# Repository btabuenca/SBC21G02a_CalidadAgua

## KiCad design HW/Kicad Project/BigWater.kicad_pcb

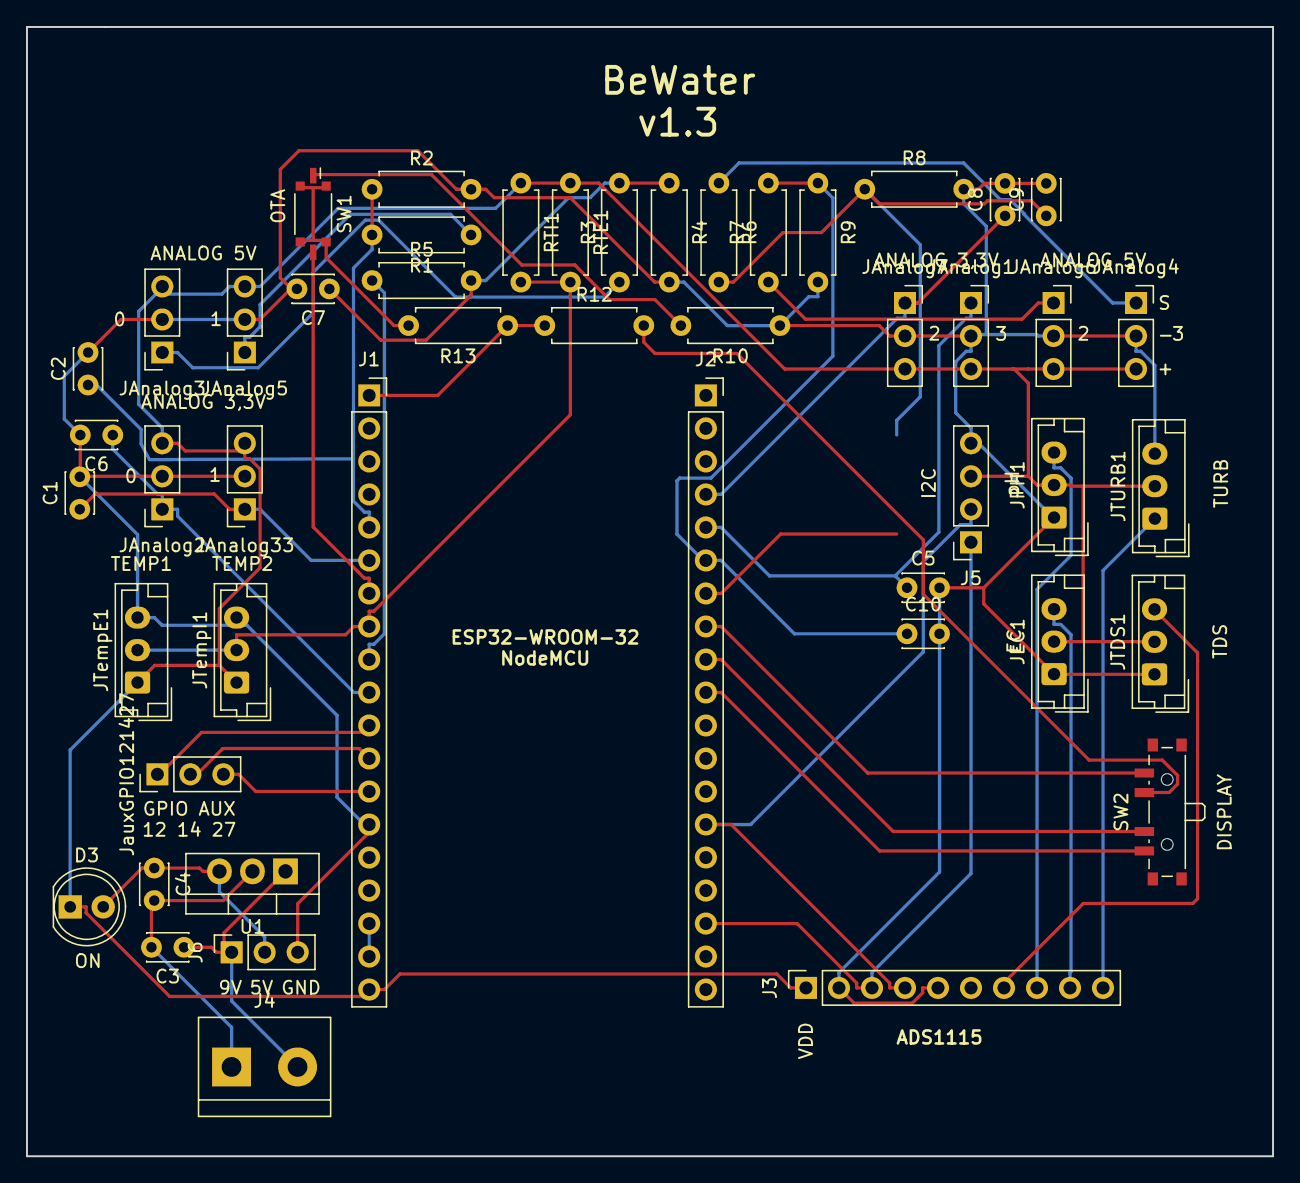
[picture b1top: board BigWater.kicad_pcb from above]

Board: 2 copper layers, 95.9 x 86.9 mm, 49 parts (0 on the bottom side), 37 nets.

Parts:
C1, C2, C4, C5, C6, C7, C8, C9, C10: 0.1u; C_Disc_D3.0mm_W2.0mm_P2.50mm
C3: 0.33u; C_Disc_D3.0mm_W2.0mm_P2.50mm
D3: LED; LED_D5.0mm
J1, J2: Conn_01x19; PinSocket_1x19_P2.54mm_Vertical
J3: ADS1115; PinSocket_1x10_P2.54mm_Vertical
J4: Conn_01x02; TerminalBlock_bornier-2_P5.08mm
J5: I2C; PinSocket_1x04_P2.54mm_Vertical
J6: Conn_01x03; PinSocket_1x03_P2.54mm_Vertical
JAnalog1, JAnalog2, JAnalog3, JAnalog4, JAnalog5, JAnalog6, JAnalog7, JAnalog33: Conn_01x03; PinSocket_1x03_P2.54mm_Vertical
JEC1: Conn_01x03; JST_EH_B3B-EH-A_1x03_P2.50mm_Vertical
JPH1: Conn_01x03; JST_EH_B3B-EH-A_1x03_P2.50mm_Vertical
JTDS1: Conn_01x03; JST_EH_B3B-EH-A_1x03_P2.50mm_Vertical
JTURB1: Conn_01x03; JST_EH_B3B-EH-A_1x03_P2.50mm_Vertical
JTempE1: Conn_01x03; JST_EH_B3B-EH-A_1x03_P2.50mm_Vertical
JTempI1: Conn_01x03; JST_EH_B3B-EH-A_1x03_P2.50mm_Vertical
JauxGPIO121427: Conn_01x03; PinHeader_1x03_P2.54mm_Vertical
R1, R3, R6, R7, R10, R12, R13: 1K; R_Axial_DIN0207_L6.3mm_D2.5mm_P7.62mm_Horizontal
R2, R4, R8, R9: 2K; R_Axial_DIN0207_L6.3mm_D2.5mm_P7.62mm_Horizontal
R5: 100; R_Axial_DIN0207_L6.3mm_D2.5mm_P7.62mm_Horizontal
RTE1: 4K7; R_Axial_DIN0207_L6.3mm_D2.5mm_P7.62mm_Horizontal
RTI1: 4K7; R_Axial_DIN0207_L6.3mm_D2.5mm_P7.62mm_Horizontal
SW1: SW_SPDT; SW_DIP_SPSTx01_Slide_Copal_CVS-01xB_W5.9mm_P1mm
SW2: SW_SP3T; SW_SP3T_PCM13
U1: LM7805_TO220; TO-220-3_Vertical

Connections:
5V: D3.1, J1.19, J3.1, J5.3, JAnalog1.3, JAnalog2.3, JAnalog3.3, JAnalog4.3, JAnalog5.3, JAnalog6.3, JAnalog7.3, JAnalog33.3, JEC1.2, JPH1.2, JTDS1.2, JTURB1.2, JTempE1.1, JTempI1.1, RTE1.1, RTI1.1
33V: J1.1, R12.1, R13.1
ANALOG5: C2.1, J1.5, R1.2, R2.1
ANALOG5b: J1.9, R5.1
ANALOG5c: C9.1, J2.7, R6.2, R8.1
ANALOG5d: C10.1, J2.6, R7.2, R9.1
ANALOG33: C1.1, J1.6, JAnalog33.1
ANALOG33b: C6.1, J1.10, JAnalog2.1
ANALOG33c: C5.1, J2.5, JAnalog1.1
ANALOG33d: C8.1, J2.4, JAnalog7.1
Aux12: J1.13, JauxGPIO121427.3
Aux14: J1.12, JauxGPIO121427.2
Aux27: J1.11, JauxGPIO121427.1
EC: J3.9, JEC1.3
GND: C1.2, C2.2, C5.2, C6.2, C7.2, C8.2, C9.2, C10.2, J1.14, J3.2, J3.5, J5.4, J6.3, JAnalog1.2, JAnalog2.2, JAnalog3.2, JAnalog4.2, JAnalog5.2, JAnalog6.2, JAnalog7.2, JAnalog33.2, JEC1.1, JPH1.1, JTDS1.1, JTURB1.3, JTempE1.3, JTempI1.3, R2.2, R4.2, R8.2, R9.2, R10.1
unnamed: C3.1, J4.2, J6.1, U1.1
unnamed: C3.2, C4.2, J4.1, U1.2
unnamed: C4.1, D3.2, J6.2, U1.3
unnamed: C7.1, R3.2, R4.1, R5.2
unnamed: JAnalog3.1, R3.1
unnamed: JAnalog4.1, R6.1
unnamed: JAnalog5.1, R1.1
unnamed: JAnalog6.1, R7.1
unnamed: R10.2, SW1.1
unnamed: R12.2, SW2.3
unnamed: R13.2, SW1.3
OTA: J1.7, SW1.2
OneWire: J1.8, JTempE1.2, JTempI1.2, RTE1.2, RTI1.2
SCL: J2.17, J3.3, J5.1
SDA: J2.14, J3.4, J5.2
SPI_HD: J1.17, J1.18
TDS: J3.7, JTDS1.3
TURB: J3.10, JTURB1.1
display1: J2.10, SW2.1
display2: J2.9, SW2.2
display3: J2.8, SW2.4
pH: J3.8, JPH1.3

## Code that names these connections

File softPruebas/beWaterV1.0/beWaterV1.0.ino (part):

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#define TOKEN               "ESP32_BeWater_SBC"
#define THINGSBOARD_SERVER  "thingsboard.cloud"
#define SERIAL_DEBUG_BAUD 115200
#define PIN_OTA 34
#define PERIODO 10
#define SEGUNDOSOTA 300 //Segundos que permanecerá el dispositivo disponible para OTA
#define CALVTURB 0
#define KHIGHEC 0.9
#define KLOWEC 1.1
#define OFFSETPH 0
#define uS_TO_S_FACTOR 1000000ULL  
#define DISPLAY1 32
#define DISPLAY2 35
#define DISPLAY3 27
#define PIN_TEMP 33
#define SAMPLESpH 16
#define SECS_DISPLAY 30
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WebServer server(80);

//Sensors
OneWire oneWireObjeto(PIN_TEMP);
DallasTemperature sensorDS18B20(&oneWireObjeto);
WiFiClient espClient;
ThingsBoard tb(espClient);
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   
   sensorDS18B20.begin();
   ads.begin();
   pinMode(PIN_OTA, INPUT);
   pinMode(DISPLAY1, INPUT);
   pinMode(DISPLAY2, INPUT);
   pinMode(DISPLAY3, INPUT);
   attachInterrupt(DISPLAY3, isr, RISING);
   lcd.init();                      
   lcd.backlight();
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void loop() {
  wakeup();
  initConection();
  if(digitalRead(PIN_OTA) == RISING){
    ndor=hour;
    }
  if(ndor==hour){      // ciclos para ser lanzado cada hora
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
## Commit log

2021-10-28 Subidos programas de obtencion de temperatura por puerto 33
2021-10-28 Subidos ficheros para funcionamiento de thingsboard
2021-11-04 Cambios en el pin de entrada de datos. Ahora es el 33
2021-11-04 Conseguida conexión con thingsboard
2021-11-04 Conseguida conexión de temp y turbidez
2021-11-18 Reestructurado el programa
2021-11-18 Falta revisar funcion de transformacion de voltajea turbidez
2021-11-23 Arreglado CAD para sensor de turbidez
2021-11-24 Añadido archivo para animación inicial
2021-11-25 Añadido modo bajo consumo. En fase depruebas para ajustar función turbidez
2021-11-25 Terminada implementación de sensor turbidez
2021-11-25 Añadida funcionalidad para obtener valores de EC
2021-12-03 Añadidas librerías, ElegantOTA y TDS
2021-12-03 Añadidas algunas librerías y modificado el código para actualizaciones OTA cada hora
2021-12-04 Añadido esquemático V1
2021-12-09 Añadido despues del puente
2021-12-11 Añadidas librerias para swich de 3 posiciones
2021-12-11 Completado esuqemático. Posicionamiento de componentes en curso
2021-12-12 Añadido diseño de la PCB
2021-12-12 Añadida máscara
2021-12-12 Release beWater software 1.0
2021-12-15 Añadidos widgets y cambio de OTA a la de thingsboard
2021-12-15 Añadida funcionalidad para pantalla a modo de carrousel y cálculo automático de tiempo para la OTA
2021-12-15 Segunda versión de telemetrías simuladas
2022-01-21 Version 1.3 HW. A la espera de correcciones de Norberto
2022-01-21 Añadidas imágenes
2022-01-24 Guardado progreso día lunes
2022-01-26 Añadido esquema de montaje
